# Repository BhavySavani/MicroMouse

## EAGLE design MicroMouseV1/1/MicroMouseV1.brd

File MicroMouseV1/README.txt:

This is the first version of our Micromouse which secured 2nd position in Conscientia 2024 Technical Fest at Indian Institute of Space Science And Technology.
In this version we used the Arduino Framework to code an ESP32 board. A rotary encoder was used along with N20 motors and equipped with PID for precise control. IR sensors were used on front, right and left side for detecting walls. The bot was built using two zero PCBs stacked on each other. We powered the bot using a 11.1v 350mAh LiPo battery through a Voltage Regulator(Arduino Nano).
Floodfill algorithm was employed for path planning.
This code is for a 12x12 maze but we can use it for any even sized square shaped grid.

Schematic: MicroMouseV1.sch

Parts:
BAT: 7.4V; BATTERY
LEFT: MOTOR10MM; VIBE-MOTOR-10MM
RIGHT: MOTOR10MM; VIBE-MOTOR-10MM
U$1: TB66612FNG
U$2: ESP-WROOM-32-WOBLE
X1, X2: ENCODER_2591ENCODER_2591_THT; ENCODER_2591_THT

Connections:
+: BAT.+@1 (+)
A01: LEFT.+, U$1.A01, X1.M1
A02: LEFT.-, U$1.A02, X1.M2
AIN1: U$1.AIN1, U$2.D13
AIN2: U$1.AIN2, U$2.D12
B01: RIGHT.+, U$1.B01, X2.M1
B02: RIGHT.-, U$1.B02, X2.M2
BAT: BAT.+, U$1.VM
BIN1: U$1.BIN1, U$2.D14
BIN2: U$1.BIN2, U$2.D27
C1L: U$2.D35, X1.OUTA
C1R: U$2.D19, X2.OUTA
C2L: U$2.D34, X1.OUTB
C2R: U$2.D18, X2.OUTB
D32: U$2.D32
D33: U$2.D33
GND: BAT.-, U$1.GND, U$1.GND2, U$1.GND3, U$2.GND, X1.GND, X2.GND
PWMB: U$1.PWMA
PWML: U$1.PWMB, U$2.D25
PWMR: U$2.D26
STBY: U$1.STBY, U$2.D22
VCC: U$1.VCC, U$2.3V3, X1.VCC, X2.VCC

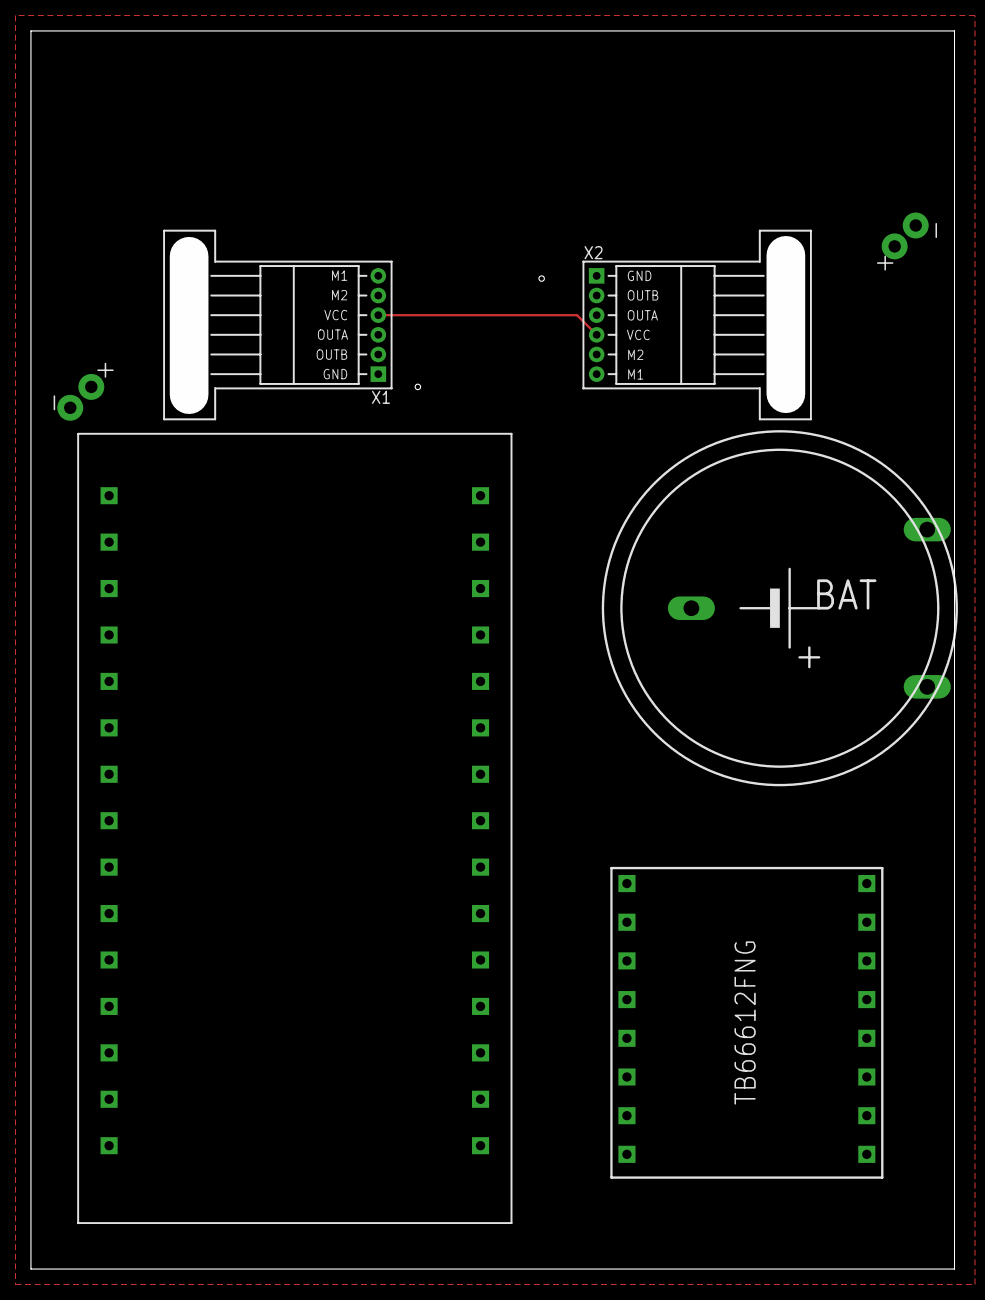
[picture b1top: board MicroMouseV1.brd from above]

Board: 2 copper layers, 57.2 x 77.5 mm, 7 parts (0 on the bottom side), 17 nets.

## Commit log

2024-10-06 Rename MicroMouseMain.brd to MicroMouseV1.brd
2024-10-06 Rename MicroMouseMain.sch to MicroMouseV1.sch
2024-10-07 Rename WhatsApp Image 2024-10-06 at 22.21.31.jpeg to MicroMouse1.jpeg
2024-10-07 Rename MicroMouse1.jpeg to MicroMouseFront.jpeg
2024-10-07 Rename WhatsApp Image 2024-10-06 at 22.21.32 (1).jpeg to MicroMouseV1.jpeg
2024-10-07 Rename MicroMouseFront.jpeg to MicroMouseFrontV1.jpeg
2024-10-07 Rename WhatsApp Image 2024-10-06 at 22.21.32.jpeg to MicroMouseV1Top.jpeg
2024-10-07 Rename WhatsApp Image 2024-10-06 at 22.21.33 (1).jpeg to MicroMouseBack.jpeg
2024-10-07 Rename MicroMouseBack.jpeg to MicroMouseBack.jpeg
2024-10-07 Rename MicroMouseV1/WhatsApp Image 2024-10-06 at 22.21.33.jpeg to MicroMouseV1SideView.jpeg
2024-10-07 Rename MicroMouseV1SideView.jpeg to MicroMouseV1/MicroMouseV1SideView.jpeg
2024-10-07 Rename MicroMouseV1/MicroMouseV1.sch to MicroMouseV1/1/MicroMouseV1.sch
2024-10-07 Rename MicroMouseV1/MicroMouseV1.brd to MicroMouseV1/1/MicroMouseV1.brd

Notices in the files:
parts and their libraries:
SparkFun-Electromechanical: Licensing: Creative Commons ShareAlike 4.0 International - https://creativecommons.org/licenses/by-sa/4.0
